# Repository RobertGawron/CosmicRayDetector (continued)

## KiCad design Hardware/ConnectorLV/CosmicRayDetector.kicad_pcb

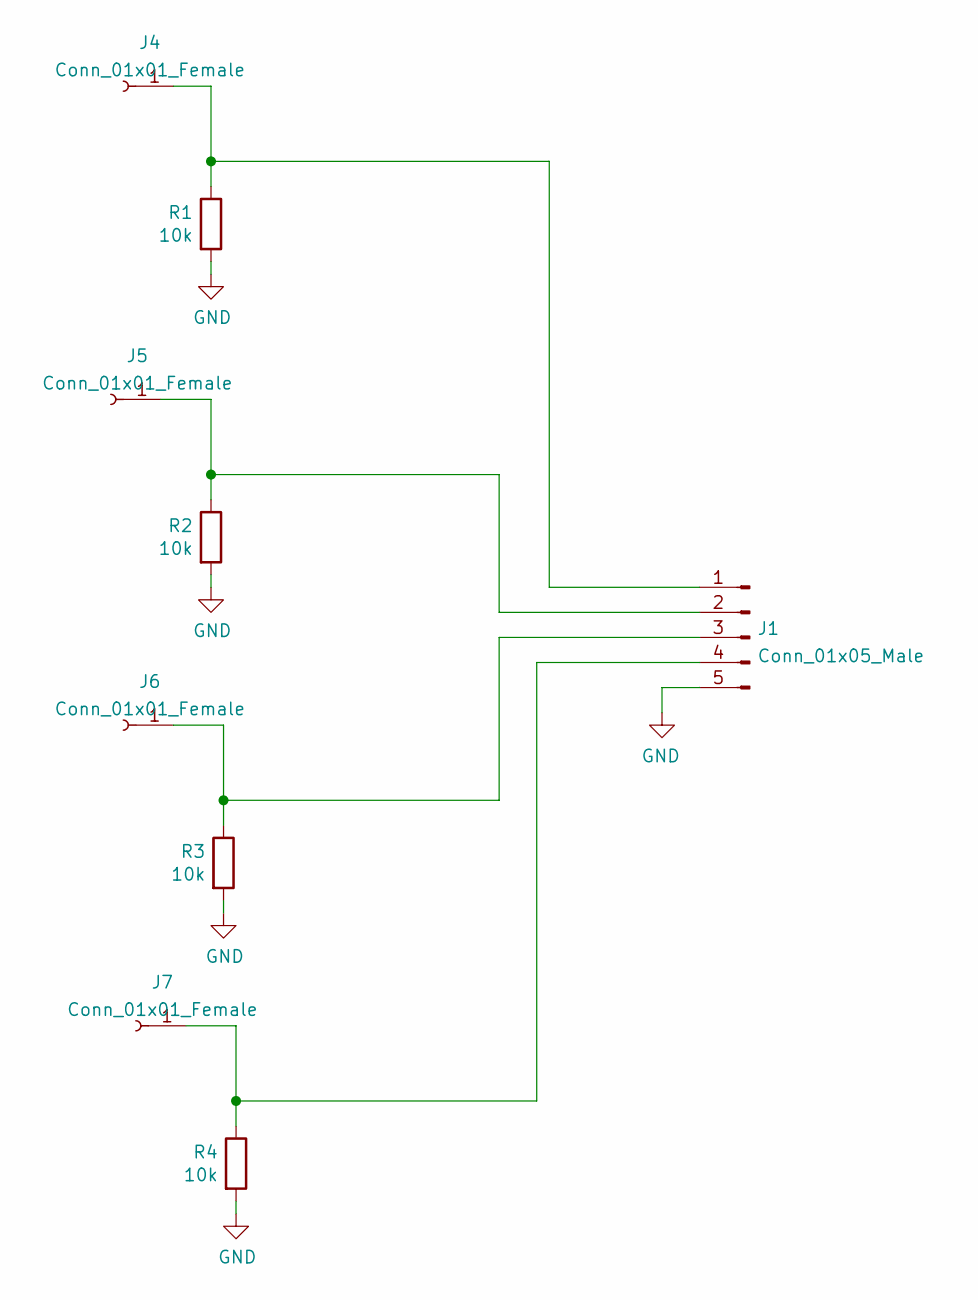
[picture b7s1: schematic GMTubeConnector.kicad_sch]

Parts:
J1: Conn_01x05_Male; PinHeader_1x05_P2.54mm_Horizontal
J4, J5, J6, J7: Conn_01x01_Female; GeigerTube
R1, R2, R3, R4: 10k; R_0805_2012Metric_Pad1.20x1.40mm_HandSolder

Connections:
GND: J1.5, R1.2, R2.2, R3.2, R4.2
unnamed: J1.1, J4.1, R1.1
unnamed: J1.2, J5.1, R2.1
unnamed: J1.3, J6.1, R3.1
unnamed: J1.4, J7.1, R4.1

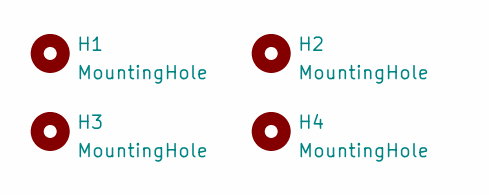
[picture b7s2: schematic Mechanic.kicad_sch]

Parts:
H1, H2, H3, H4: MountingHole; MountingHole_3.5mm

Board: 2 copper layers, 13 parts (0 on the bottom side), 5 nets, no tracks yet.

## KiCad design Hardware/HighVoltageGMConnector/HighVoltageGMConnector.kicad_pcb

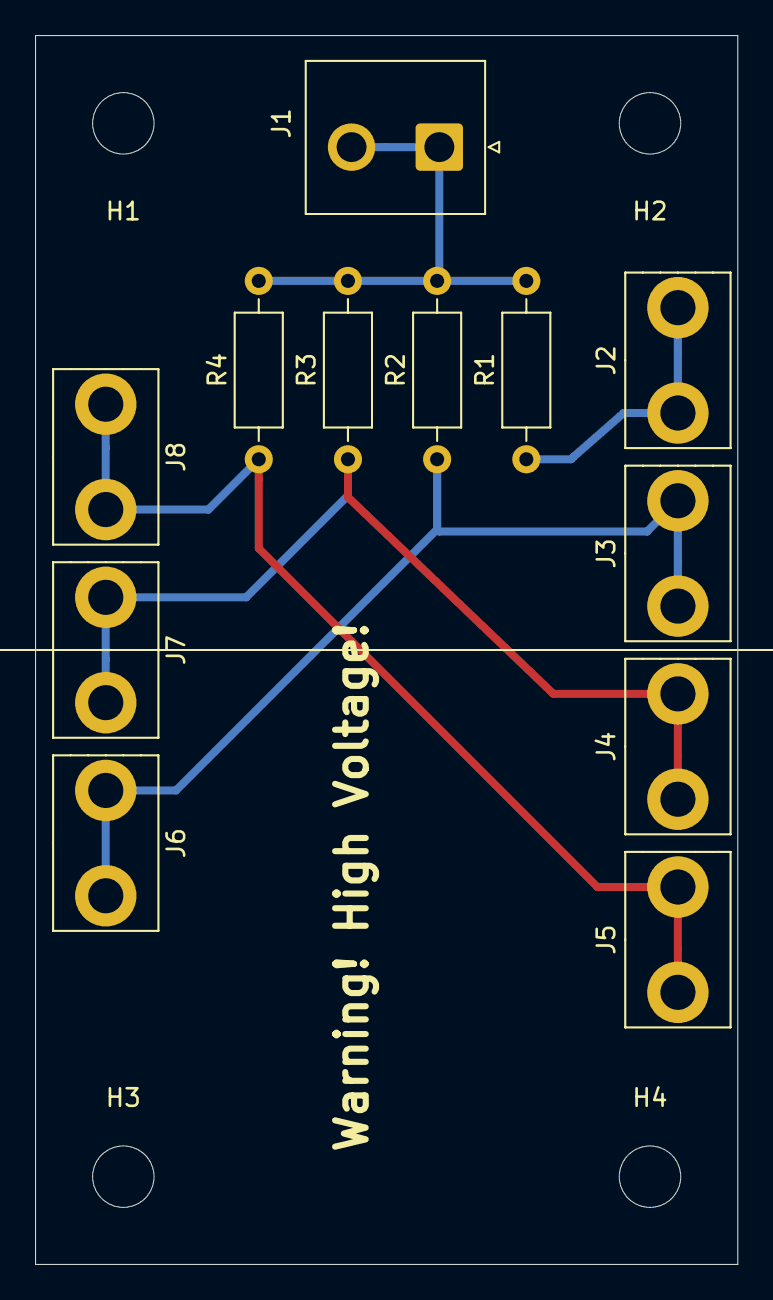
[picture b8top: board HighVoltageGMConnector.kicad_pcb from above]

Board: 2 copper layers, 40.0 x 70.0 mm, 16 parts (0 on the bottom side), 5 nets.

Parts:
H1, H2, H3, H4: MountingHole; MountingHole_3.5mm
J1: Conn_01x02_Male; JST_NV_B02P-NV_1x02_P5.00mm_Vertical
J2, J3, J4, J5, J6, J7, J8: Conn_01x01_Female; GeigerTube
R1, R2, R3, R4: 6M8; R_Axial_DIN0207_L6.3mm_D2.5mm_P10.16mm_Horizontal

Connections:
unnamed: J1.1, J1.2, R1.2, R2.2, R3.2, R4.2
unnamed: J2.1, R1.1
unnamed: J3.1, J6.1, R2.1
unnamed: J4.1, J7.1, R3.1
unnamed: J5.1, J8.1, R4.1

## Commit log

2019-05-26 draft of schemat and pcb
2019-06-01 backup copy
2019-06-01 backup
2019-06-01 draft
2019-06-02 template for software project
2019-06-02 remove temporary file
2019-06-02 roughly routed, to be polished
2019-06-04 before rename
2019-06-04 iunified names of files
2019-06-08 cleanup
2019-06-09 updated configuration
2019-06-09 draft of board connector
2019-06-09 fixzed layers
2019-06-09 draft of version without expensive connectors
2019-06-09 added pic foor readme
2019-06-15 fixed labels, changed board size
2019-06-15 added readme
2019-06-15 revision 1.0 (reworked git history)
2019-08-27 remove stm32 project
2019-08-27 fpga firmware sketch
2019-08-27 local files removed
2019-08-31 added main block diagram
2019-08-31 simulation of particle detection added
2019-08-31 added draft of architecture
2019-08-31 picture to used in README.md
2019-08-31 updates fater fpga was choosen
2019-08-31 add travis config to check docs correctness
2019-08-31 added build status
2019-09-01 draft of mechanical paer
2019-09-01 dummy shape
2019-09-02 draft of gm tube
2019-09-02 middle part of gm tube
2019-09-02 gm tube body dimensions fized
2019-09-02 correct gm tube model
2019-09-02 more intuitive subparts names
2019-09-02 rouch view ow the device will looks like
2019-09-03 correct import of pcb
2019-09-03 sheets updated to current design
2019-09-03 removed parts not needed due to fpga use
2019-09-03 pcb dimension and socket holes placement
2019-09-03 crd, hw power, gm tube placed roughly ok
2019-09-03 3d model for GM connector
2019-09-03 fix #30
2019-09-04 added li-ion charger
2019-09-04 added sheet for movement controol
2019-09-05 draft of a holder
2019-09-05 completed draft of a holder on bearing side
2019-09-05 added screw taps
2019-09-05 perspective change
2019-09-05 fix #43
2019-09-05 folder structure simplification
2019-09-05 added GM VH connector board
2019-09-05 handler resized
2019-09-05 fpga board mockup for freecad
2019-09-05 added fpga board mock
2019-09-05 added device render to README.md
2019-09-06 fix #55
2019-09-06 imported fpga board
2019-09-06 sketch created
2019-09-06 paritialy added screw mounting points
2019-09-06 holes for scre placed correctly
2019-09-06 constrains to mounting holes
2019-09-06 i give up, the wheel is good enough
2019-09-06 rotor screws in correct place
2019-09-06 changed 3d printg color to more apealing
2019-09-06 changed gm tube color and material
2019-09-06 draft of step motor driver
2019-09-08 initial version
2019-09-08 fixed file name
2019-09-08 fixed size
2019-09-08 folder structure cleanup
2019-09-09 scad files refactored to sepatrate modules
2019-09-09 moving to OpenSCAD
2019-09-09 refactored hardcoded values and variable names
2019-09-09 draft of gm counter holder
2019-09-10 cleaned rotor related files
2019-09-10 further cleanup
2019-09-10 further code cleanup
2019-09-10 holder for gm counter
2019-09-10 fixed incorrect dimensions
2019-09-11 added/removed new lines to make consistent
2019-09-29 fully routed
2019-09-29 silscreen laver placement
2019-09-29 use stl imported models for better render quality
2019-10-12 improved naming, removed tabs
2019-10-12 better file names
2019-10-12 fixed all tabs to spaces
2019-10-12 module names change
2019-10-12 further namining improvement
2019-11-01 more details
2019-11-01 reduced spaces between components
2020-10-28 folder structure cleanup, move from travis to github actions
2020-10-29 add design files for mechanic overview
2020-10-30 decrease physical dimmensions of the device (not completed)
2020-10-31 finished mechanical overview design
2020-10-31 Add render of the mechanical overview.
2020-11-01 fix #54, fix: #84
2020-11-01 make architecture diagram more compacted
2020-11-01 improve mechanical section of main README, move .gitignore for hardware part to Hardware directory
2020-11-01 finished design of electronic circuit for detector
2020-11-01 done component placement on pcb and a draft of routing
2020-11-02 finished pcb design
2020-11-02 documentation fixes for hardware render
2020-11-06 Fix grammar mistakes (found by Code Spell Checker add-on in VSCode). (fix #94)
2020-11-09 Improve PCB design (fix: #97)
2021-06-20 add bom
2021-07-17 fix #103 #104 #105 #106
2021-07-25 fix #109, fix #110
2021-08-07 fix #117
2021-08-15 cleanup after transition to KiCad6
2022-08-03 added list of componnts t be bought and links where to buy them, todo: find a way to do it from kicad directly
2022-08-06 split pcb dsign to separate pcbs
2022-08-20 split PCB into separate designs
2022-08-25 unify all boards into a single one again, but eliminate connectors and dcrease number of mechanical parts
2024-08-17 this is what was send for pcb production
2024-09-09 add hw version 3.0 and cleanup of the docs
2024-09-14 add hw version 3.0
